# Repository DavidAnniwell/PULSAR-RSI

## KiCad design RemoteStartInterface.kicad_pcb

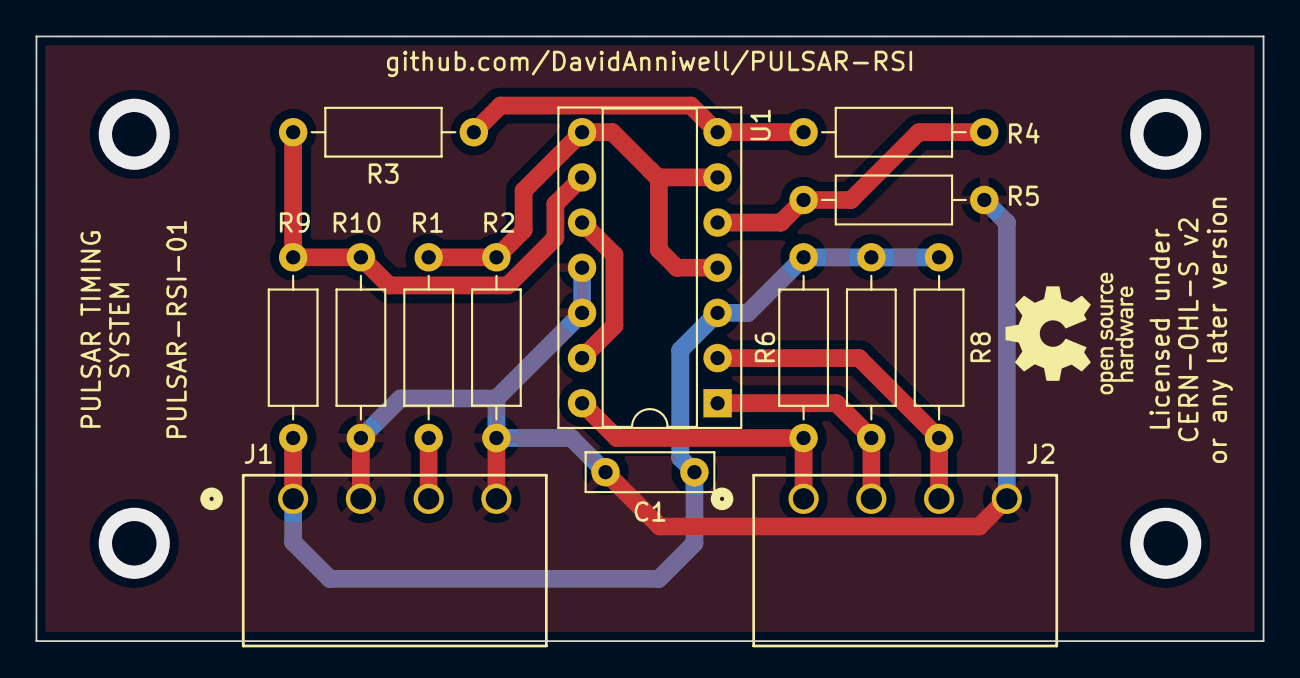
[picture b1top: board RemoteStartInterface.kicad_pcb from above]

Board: 2 copper layers, 69.0 x 34.0 mm, 14 parts (0 on the bottom side), 11 nets.

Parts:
C1: 100n; C_Rect_L7.0mm_W2.0mm_P5.00mm
J1, J2: 1803293; CONN_1803293_PXC
R1, R2, R3, R4, R5, R6, R7, R8, R9, R10: 1k; R_Axial_DIN0207_L6.3mm_D2.5mm_P10.16mm_Horizontal
U1: LM339; DIP-14_W7.62mm_Socket

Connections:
+5VD: C1.1, J1.1, R6.1, R7.1, R8.1, R9.1, U1.3 (V+)
GND: C1.2, J1.2, J1.4, J2.4, R2.2, R5.2, R10.2, U1.11 (+), U1.12 (V-)
unnamed: J1.3, R1.1
unnamed: J2.1, R6.2, U1.14
unnamed: J2.2, R7.2, U1.1
unnamed: J2.3, R8.2, U1.2
unnamed: R4.2, R5.1, U1.5 (+)
unnamed: R1.2, R2.1, U1.4 (-), U1.6 (-), U1.8 (-)
unnamed: R3.2, R4.1, U1.7 (+)
unnamed: U1.10 (-), U1.13
unnamed: R3.1, R9.2, R10.1, U1.9 (+)

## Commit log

2024-04-06 Update LICENSE
2024-04-14 Initial commit
    Completed version 1 PCB

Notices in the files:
RemoteStartInterface.kicad_pcb:
Licensed under
CERN-OHL-S v2
Copyright David Anniwell 2024.
This source describes Open Hardware and is licensed under the CERN-
under the terms of the CERN-OHL-S v2
(https://ohwr.org/cern ohl s v2.txt ).
QUALITY AND FITNESS FOR A PARTICULAR PURPOSE. Please see
the CERN-OHL-S v2 for applicable conditions.
As per CERN-OHL-S v2 section 4, should You produce hardware based
